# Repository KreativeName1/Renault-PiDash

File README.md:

# Renault-PiDash
digital gauge pods for the Renault 19 and other cars

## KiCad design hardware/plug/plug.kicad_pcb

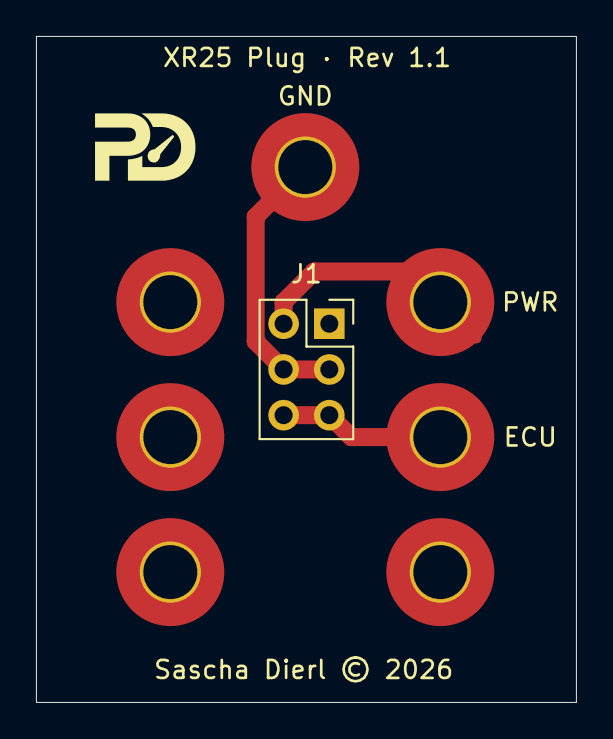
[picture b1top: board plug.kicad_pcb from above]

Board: 2 copper layers, 30.0 x 37.0 mm, 8 parts (0 on the bottom side), 3 nets.

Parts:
12: MountingHole_Pad; MountingHole_3mm_Pad_TopBottom
ECU: MountingHole_Pad; MountingHole_3mm_Pad_TopBottom
GND: MountingHole_Pad; MountingHole_3mm_Pad_TopBottom
H2, H3, H4: MountingHole_Pad; MountingHole_3mm_Pad_TopBottom
J1: Conn_02x03_Odd_Even; PinSocket_2x03_P2.54mm_Vertical
PWR: MountingHole_Pad; MountingHole_3mm_Pad_TopBottom

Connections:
unnamed: J1.2, PWR.1 (1_1)
unnamed: GND.1 (1_1), J1.3, J1.4
unnamed: ECU.1 (1_1), J1.5, J1.6

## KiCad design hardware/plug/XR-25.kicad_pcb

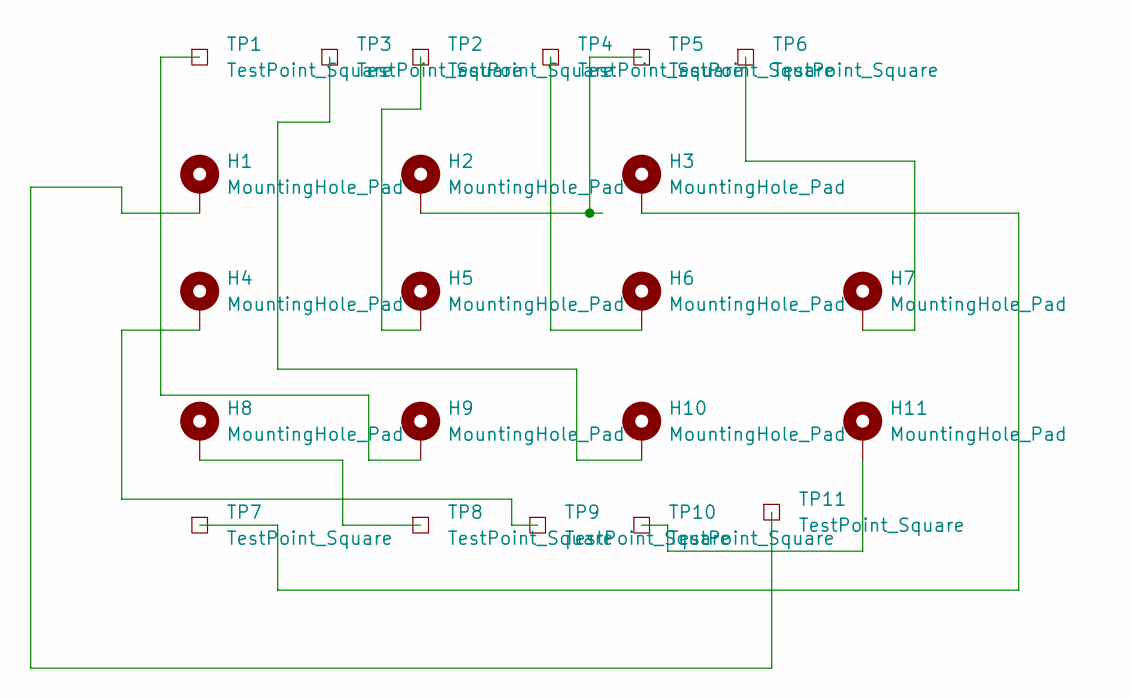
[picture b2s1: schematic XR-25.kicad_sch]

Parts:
H1, H2, H3, H4, H5, H6, H7, H8, H9, H10, H11: MountingHole_Pad; MountingHole_3mm_Pad_TopBottom
TP1, TP2, TP3, TP4, TP5, TP6, TP7, TP8, TP9, TP10, TP11: TestPoint_Square; TestPoint_Keystone_5015_Micro_Mini

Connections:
unnamed: H1.1 (1_1), TP11.1 (1_1)
unnamed: H2.1 (1_1), TP5.1 (1_1)
unnamed: H3.1 (1_1), TP7.1 (1_1)
unnamed: H4.1 (1_1), TP9.1 (1_1)
unnamed: H5.1 (1_1), TP2.1 (1_1)
unnamed: H6.1 (1_1), TP4.1 (1_1)
unnamed: H7.1 (1_1), TP6.1 (1_1)
unnamed: H8.1 (1_1), TP8.1 (1_1)
unnamed: H9.1 (1_1), TP1.1 (1_1)
unnamed: H10.1 (1_1), TP3.1 (1_1)
unnamed: H11.1 (1_1), TP10.1 (1_1)

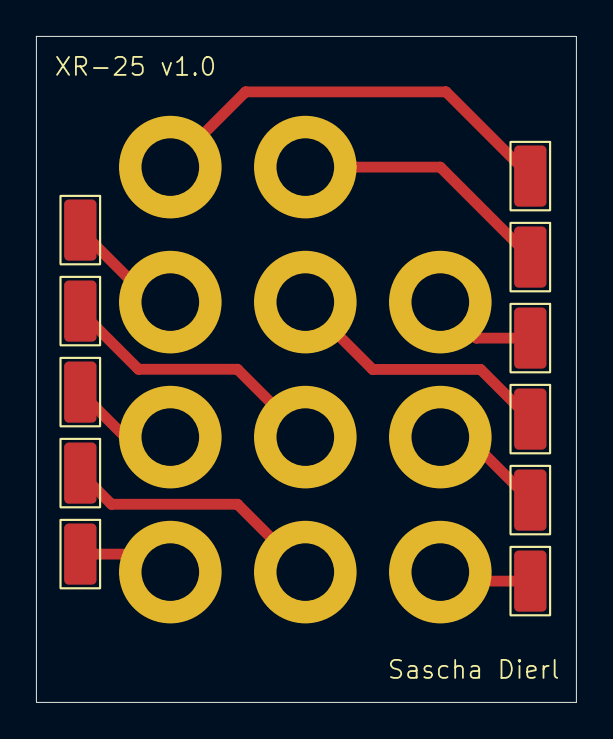
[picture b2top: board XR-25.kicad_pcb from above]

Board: 2 copper layers, 30.0 x 37.0 mm, 22 parts (0 on the bottom side), 11 nets.

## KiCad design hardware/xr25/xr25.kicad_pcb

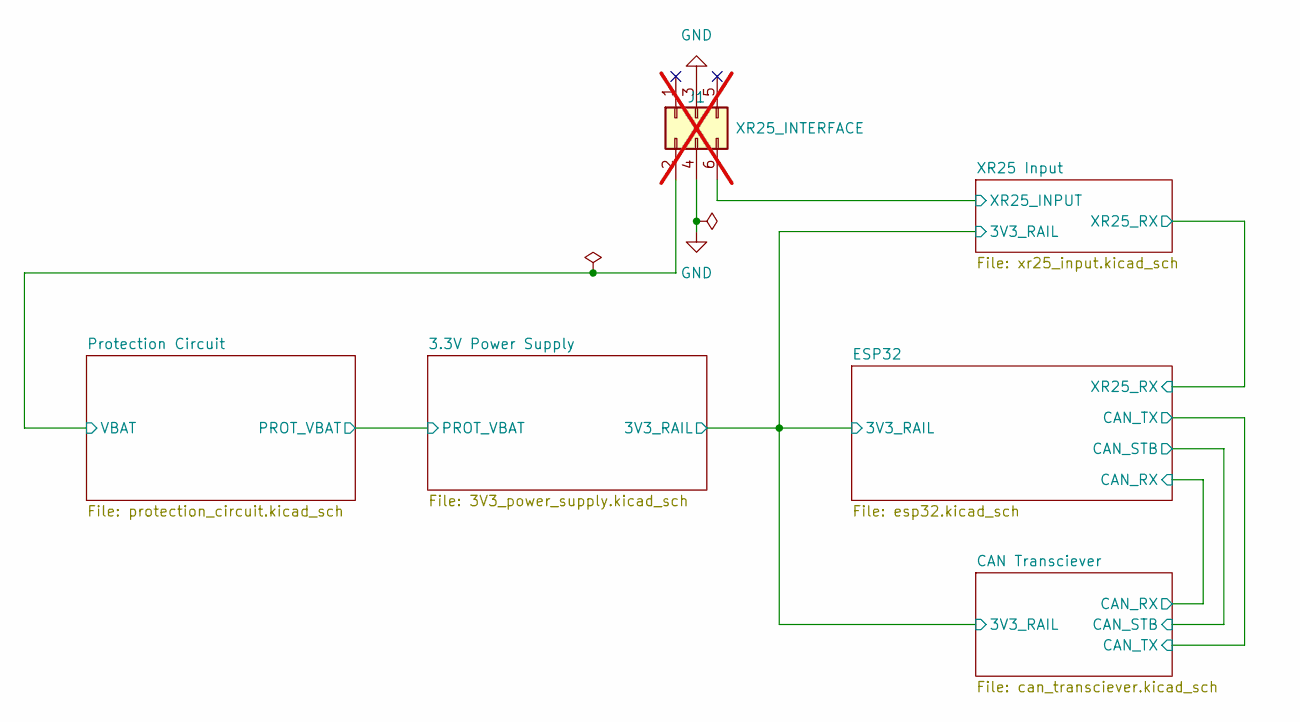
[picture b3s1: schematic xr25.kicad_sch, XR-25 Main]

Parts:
J1: XR25_INTERFACE; PinHeader_2x03_P2.54mm_Vertical; not fitted

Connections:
/Protection Circuit/VBAT: J1.2; also elsewhere on the board
/XR25 Input/XR25_INPUT: J1.6; also elsewhere on the board
GND: J1.3, J1.4; also elsewhere on the board

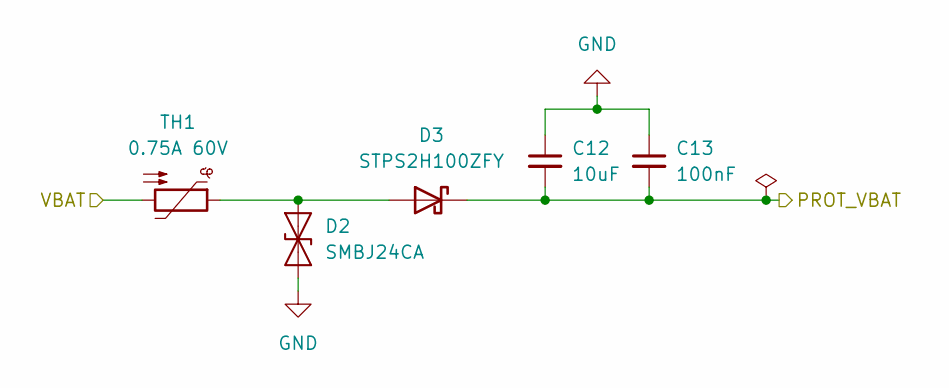
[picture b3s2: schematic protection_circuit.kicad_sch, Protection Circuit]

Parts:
C12: 10uF; C_1210_3225Metric; LCSC Part # C49296968
C13: 100nF; C_0805_2012Metric; LCSC Part # C28233
D2: SMBJ24CA; C425875_SMB_L4_3-W3_6-LS5_4-BI; LCSC Part # C425875
D3: STPS2H100ZFY; C2969868_SOD-123FL_L2_6-W1_6-LS3_5-FD; LCSC Part # C2969868
TH1: 0.75A 60V; C910836_F2018; LCSC Part # C910836

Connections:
/3.3V Power Supply/PROT_VBAT: C12.2, C13.2, D3.1 (K); also elsewhere on the board
/Protection Circuit/VBAT: TH1.2; also elsewhere on the board
GND: C12.1, C13.1, D2.1 (A1); also elsewhere on the board
unnamed: D2.2 (A2), D3.2 (A), TH1.1

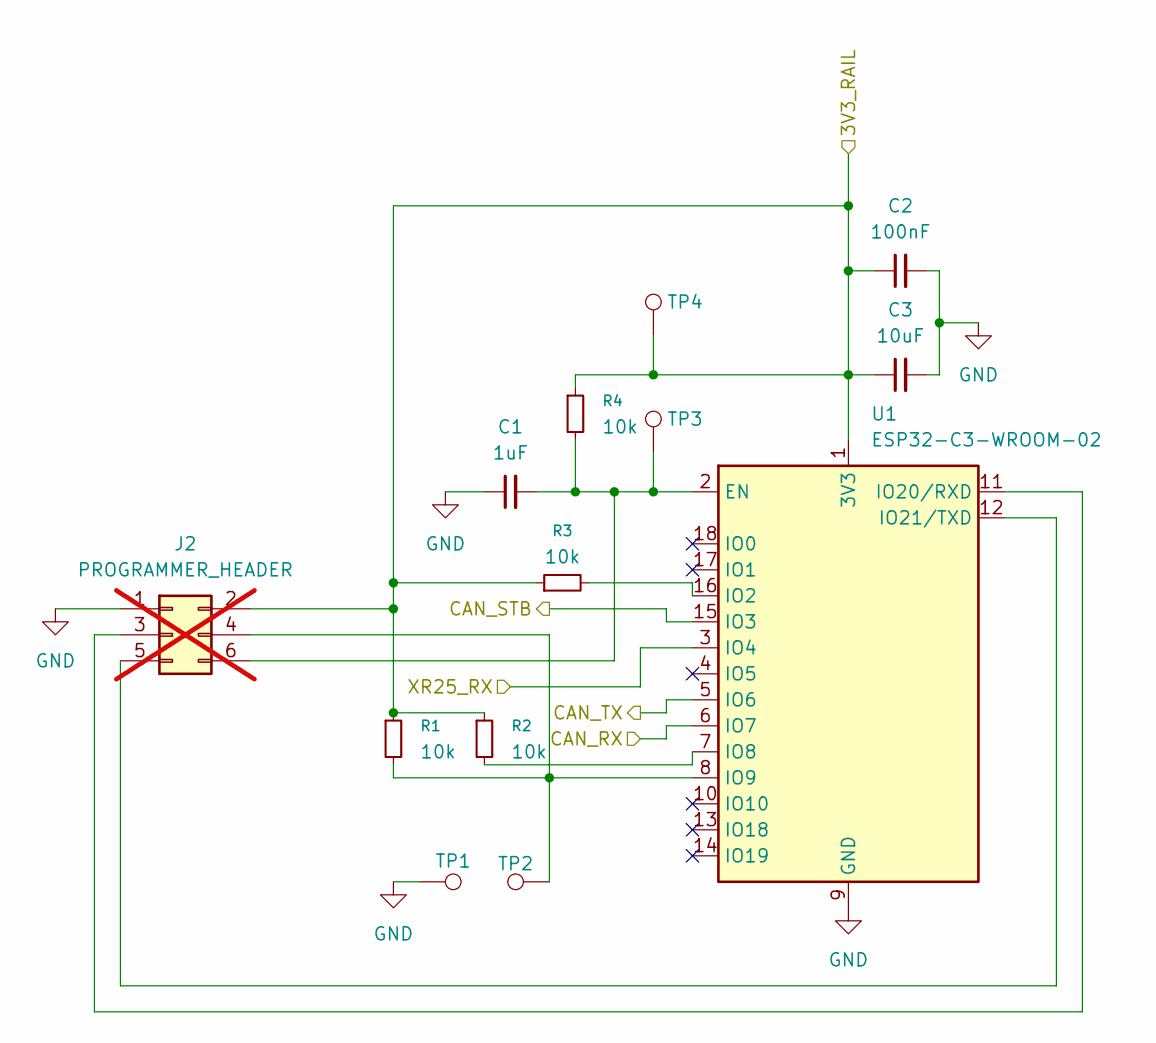
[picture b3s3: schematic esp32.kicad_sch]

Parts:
C1: 1uF; C_0603_1608Metric; LCSC Part # C15849
C2: 100nF; C_0603_1608Metric; LCSC Part # C14663
C3: 10uF; C_0805_2012Metric; LCSC Part # C15850
J2: PROGRAMMER_HEADER; PinHeader_2x03_P2.54mm_Vertical; not fitted
R1, R2, R3, R4: 10k; R_0603_1608Metric; LCSC Part # C25804
TP1: GND; TestPoint_Pad_D1.5mm
TP2: BOOT; TestPoint_Pad_D1.5mm
TP3: ENABLE; TestPoint_Pad_D1.5mm
TP4: 3V3; TestPoint_Pad_D1.5mm
U1: ESP32-C3-WROOM-02; LCSC Part # C2934560

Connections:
/3.3V Power Supply/3V3_RAIL: C2.1, C3.1, J2.2, R1.1, R2.1, R3.1, R4.1, TP4.1 (1_1), U1.1 (3V3); also elsewhere on the board
/CAN Transciever/CAN_RX: U1.6 (IO7); also elsewhere on the board
/CAN Transciever/CAN_STB: U1.15 (IO3); also elsewhere on the board
/CAN Transciever/CAN_TX: U1.5 (IO6); also elsewhere on the board
/ESP32/XR25_RX: U1.3 (IO4); also elsewhere on the board
GND: C1.1, C2.2, C3.2, J2.1, TP1.1 (1_1), U1.9 (GND), U1.19 (GND); also elsewhere on the board
unnamed: J2.3, U1.11 (IO20/RXD)
unnamed: J2.4, R1.2, TP2.1 (1_1), U1.8 (IO9)
unnamed: J2.5, U1.12 (IO21/TXD)
unnamed: C1.2, J2.6, R4.2, TP3.1 (1_1), U1.2 (EN)
unnamed: R3.2, U1.16 (IO2)
unnamed: R2.2, U1.7 (IO8)

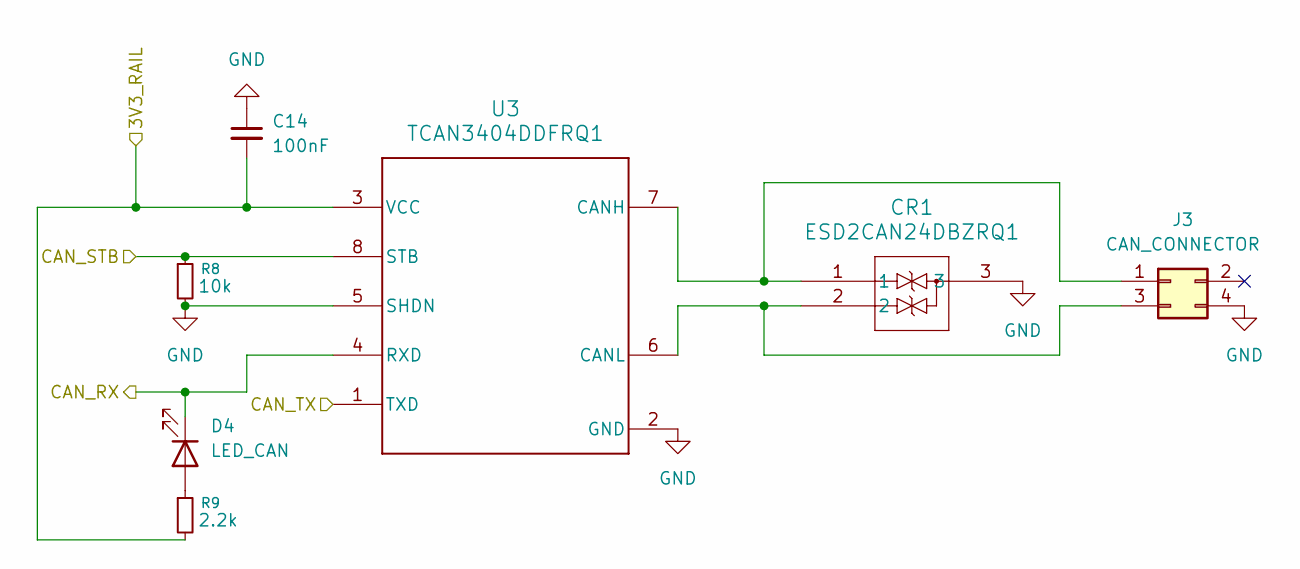
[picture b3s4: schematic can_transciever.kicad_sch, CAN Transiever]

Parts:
C14: 100nF; C_0603_1608Metric; LCSC Part # C14663
CR1: ESD2CAN24DBZRQ1; SOT-23_DBZ_TEX; LCSC Part # C5736151
D4: LED_CAN; C125098_LED0603-RD; LCSC Part # C125098
J3: CAN_CONNECTOR; C505218_CONN-SMD_430450406
R8: 10k; R_0603_1608Metric; LCSC Part # C25804
R9: 2.2k; R_0603_1608Metric; LCSC Part # C4190
U3: TCAN3404DDFRQ1; DDF0008A-IPC_A; LCSC Part # C32428067

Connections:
/3.3V Power Supply/3V3_RAIL: C14.2, R9.2, U3.3 (VCC); also elsewhere on the board
/CAN Transciever/CAN_RX: D4.1 (K), U3.4 (RXD); also elsewhere on the board
/CAN Transciever/CAN_STB: R8.1, U3.8 (STB); also elsewhere on the board
/CAN Transciever/CAN_TX: U3.1 (TXD); also elsewhere on the board
GND: C14.1, CR1.3, J3.4, R8.2, U3.2 (GND), U3.5 (SHDN); also elsewhere on the board
unnamed: D4.2 (A), R9.1
unnamed: CR1.1, J3.1, U3.7 (CANH)
unnamed: CR1.2, J3.3, U3.6 (CANL)

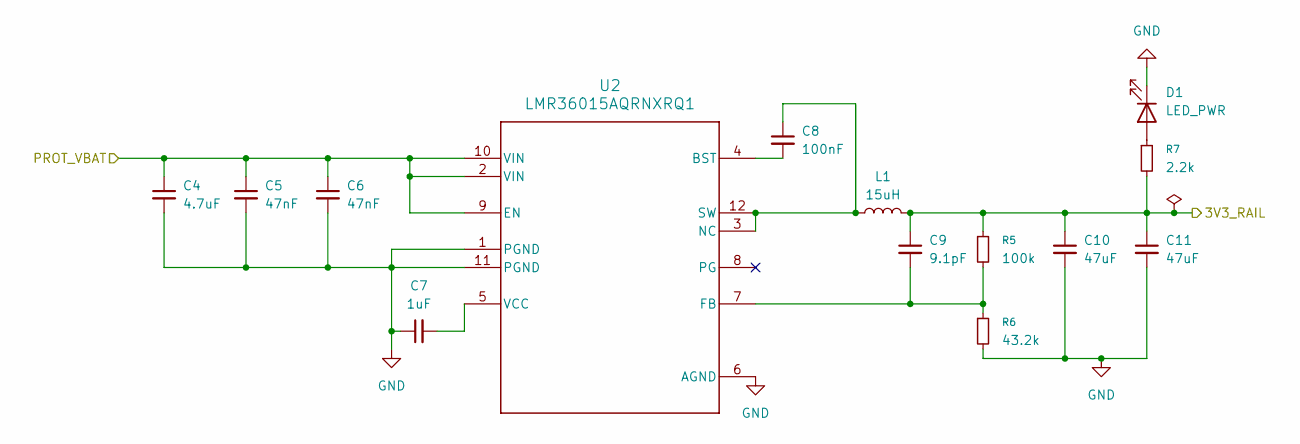
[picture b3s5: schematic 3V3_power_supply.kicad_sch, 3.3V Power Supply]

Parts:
C4: 4.7uF; C_1206_3216Metric; LCSC Part # C51205
C5, C6: 47nF; C_0603_1608Metric; LCSC Part # C1622
C7: 1uF; C_0603_1608Metric; LCSC Part # C15849
C8: 100nF; C_0603_1608Metric; LCSC Part # C14663
C9: 9.1pF; C_0603_1608Metric; LCSC Part # C61817
C10, C11: 47uF; C_1210_3225Metric; LCSC Part # C84494
D1: LED_PWR; C2286_LED-SMD_L1_6-W0_8-R-RD; LCSC Part # C2286
L1: 15uH; C83374_IND-SMD_L6_0-W6_0_SWPA6045S; LCSC Part # C83374
R5: 100k; R_0603_1608Metric; LCSC Part # C25803
R6: 43.2k; R_0603_1608Metric; LCSC Part # C23053
R7: 2.2k; R_0603_1608Metric; LCSC Part # C4190
U2: LMR36015AQRNXRQ1; RNX0012B; LCSC Part # C2863325

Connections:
/3.3V Power Supply/3V3_RAIL: C9.1, C10.1, C11.1, L1.2, R5.1, R7.2; also elsewhere on the board
/3.3V Power Supply/PROT_VBAT: C4.1, C5.1, C6.1, U2.2 (VIN), U2.9 (EN), U2.10 (VIN); also elsewhere on the board
GND: C4.2, C5.2, C6.2, C7.1, C10.2, C11.2, D1.1 (K), R6.2, U2.1 (PGND), U2.6 (AGND), U2.11 (PGND); also elsewhere on the board
unnamed: D1.2 (A), R7.1
unnamed: C8.2, U2.4 (BST)
unnamed: C9.2, R5.2, R6.1, U2.7 (FB)
unnamed: C8.1, L1.1, U2.3 (NC), U2.12 (SW)
unnamed: C7.2, U2.5 (VCC)

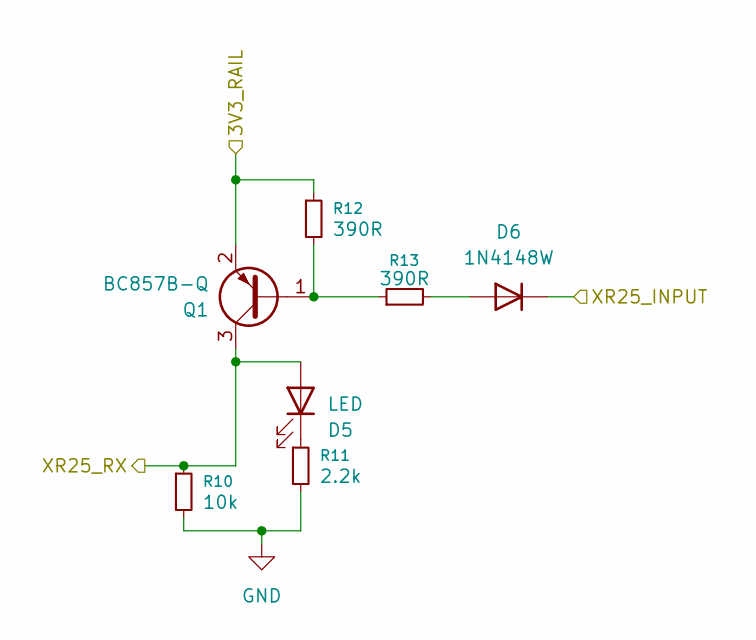
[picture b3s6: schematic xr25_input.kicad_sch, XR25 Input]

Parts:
D5: LED; C2287_LED0603-R-RD; LCSC Part # C2287
D6: 1N4148W; C84367_SOD-123_L2_8-W1_8-LS3_7-RD; LCSC Part # C84367
Q1: BC857B-Q; SOT-23; LCSC Part # C5121591
R10: 10k; R_0603_1608Metric; LCSC Part # C25804
R11: 2.2k; R_0603_1608Metric; LCSC Part # C4190
R12, R13: 390R; R_0603_1608Metric; LCSC Part # C23151

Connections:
/3.3V Power Supply/3V3_RAIL: Q1.2 (E), R12.1; also elsewhere on the board
/ESP32/XR25_RX: D5.2 (A), Q1.3 (C), R10.1; also elsewhere on the board
/XR25 Input/XR25_INPUT: D6.1 (K); also elsewhere on the board
GND: R10.2, R11.2; also elsewhere on the board
unnamed: D5.1 (K), R11.1
unnamed: D6.2 (A), R13.2
unnamed: Q1.1 (B), R12.2, R13.1

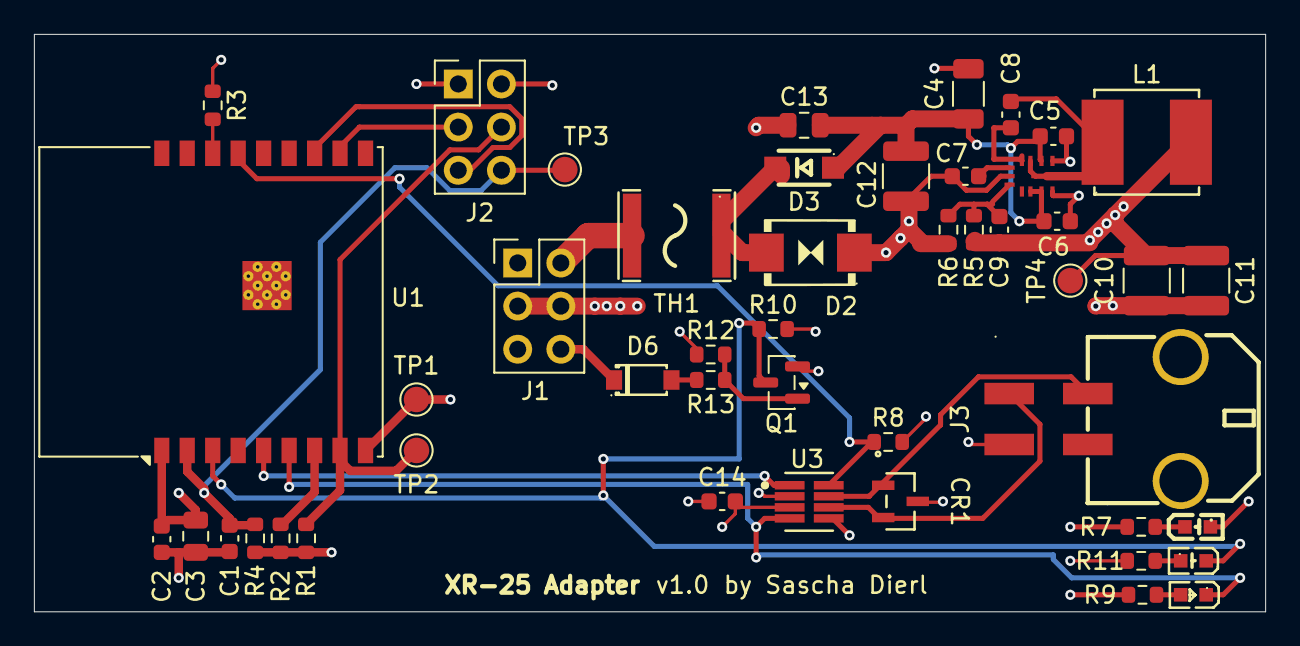
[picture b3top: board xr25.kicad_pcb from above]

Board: 4 copper layers, 72.5 x 34.0 mm, 47 parts (0 on the bottom side), 27 nets.

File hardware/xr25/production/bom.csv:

Designator,Footprint,Quantity,Value,LCSC Part #
"C1, C7",0603,2,1uF,C15849
"C10, C11",1210,2,47uF,C84494
C12,1210,1,10uF,C49296968
C13,0805,1,100nF,C28233
"C14, C2, C8",0603,3,100nF,C14663
C3,0805,1,10uF,C15850
C4,1206,1,4.7uF,C51205
"C5, C6",0603,2,47nF,C1622
C9,0603,1,9.1pF,C61817
CR1,SOT-23_DBZ_TEX,1,ESD2CAN24DBZRQ1,C5736151
D1,C2286_LED-SMD_L1_6-W0_8-R-RD,1,LED_PWR,C2286
D2,C425875_SMB_L4_3-W3_6-LS5_4-BI,1,SMBJ24CA,C425875
D3,C2969868_SOD-123FL_L2_6-W1_6-LS3_5-FD,1,STPS2H100ZFY,C2969868
D4,C125098_LED0603-RD,1,LED_CAN,C125098
D5,C2287_LED0603-R-RD,1,LED,C2287
D6,C84367_SOD-123_L2_8-W1_8-LS3_7-RD,1,1N4148W,C84367
J3,C505218_CONN-SMD_430450406,1,CAN_CONNECTOR,C505218
L1,C83374_IND-SMD_L6_0-W6_0_SWPA6045S,1,15uH,C83374
Q1,SOT-23,1,BC857B-Q,C5121591
"R1, R10, R2, R3, R4, R8",0603,6,10k,C25804
"R11, R7, R9",0603,3,2.2k,C4190
"R12, R13",0603,2,390R,C23151
R5,0603,1,100k,C25803
R6,0603,1,43.2k,C23053
TH1,C910836_F2018,1,0.75A 60V,C910836
U1,ESP32-C3-WROOM-02,1,ESP32-C3-WROOM-02,C2934560
U2,RNX0012B,1,LMR36015AQRNXRQ1,C2863325
U3,DDF0008A-IPC_A,1,TCAN3404DDFRQ1,C32428067

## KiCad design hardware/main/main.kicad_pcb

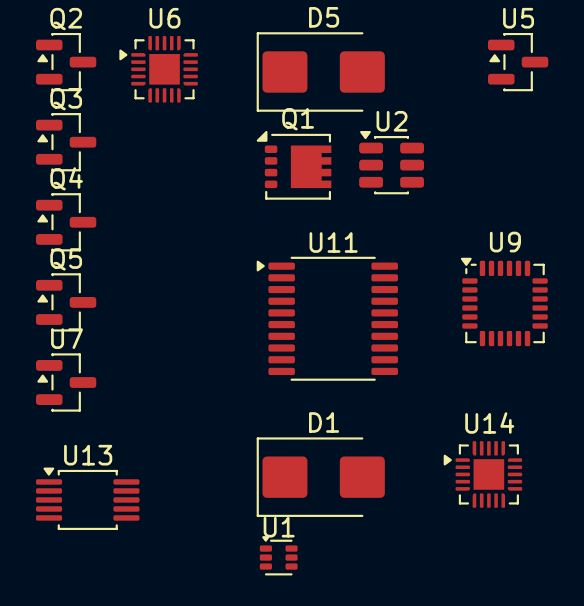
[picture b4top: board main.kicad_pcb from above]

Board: 2 copper layers, 16 parts (0 on the bottom side), 11 nets, no tracks yet.

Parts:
D1, D5: SMBJ33CA; D_SMB
Q1: DMT6007LFG-13; Diodes_PowerDI3333-8
Q2, Q3, Q4, Q5: 2N7002; SOT-23
U1: TMP112xxDRL; SOT-563
U2: LM74700; SOT-23-6
U5: MCP1799x-330xxTT; SOT-23
U6, U14: ATtiny1616-M; VQFN-20-1EP_3x3mm_P0.4mm_EP1.7x1.7mm
U7: TLV803E; SOT-23
U9: MPU-6050; InvenSense_QFN-24_4x4mm_P0.5mm
U11: MCP2515-xST; TSSOP-20_4.4x6.5mm_P0.65mm
U13: ADS1115IDGS; TSSOP-10_3x3mm_P0.5mm

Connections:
/CAM/3V3_RAIL: U1.5 (V+), U9.8 (VLOGIC), U11.20 (VDD), U13.8 (VDD), U14.4 (VCC)
/IO expansion/SCL: U1.1 (SCL), U9.23 (SCL), U13.10 (SCL), U14.1 (PA2)
/IO expansion/SDA: U1.6 (SDA), U9.24 (SDA), U13.9 (SDA), U14.20 (PA1)
/PSU/3V3 Always-On Rail/3V3_AON: U5.2 (VO), U6.4 (VCC), U7.3 (V_{DD})
/PSU/3V3 Always-On Rail/PROT_BAT: Q1.5 (D), U2.4 (CATHODE)
/PSU/PSU Controller/PSU_OFF: U6.13 (PB1), U7.2 (RESET)
GND: D1.1 (A1), D5.1 (A1), Q2.2 (S), Q3.2 (S), Q4.2 (S), Q5.2 (S), U1.2 (GND), U1.3 (ALERT), U1.4 (ADD0), U2.2 (GND), U5.1 (GND), U6.3 (GND), U6.21 (GND), U7.1 (GND), U9.1 (CLKIN), U9.11 (FSYNC), U9.18 (GND), U11.10 (VSS), U13.1 (ADDR), U13.3 (GND), U14.3 (GND), U14.21 (GND)
unnamed: D5.2 (A2), Q1.1 (S), Q1.2 (S), Q1.3 (S), U2.6 (ANODE)
unnamed: Q1.4 (G), U2.5 (GATE)
unnamed: Q3.3 (D), U6.17 (PC2)
unnamed: Q4.1 (G), Q5.1 (G)

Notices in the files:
hardware/plug/plug.kicad_pcb:
Sascha Dierl © 2026
